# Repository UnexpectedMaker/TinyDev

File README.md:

# TinyDev
TinyDev Design Files

Inlcluded in this reposity:
- EagleCAD schematics and Board layout files (Eagle 9.1.1) 
- Exported Gerber files (Gerber 274X)

Enjoy!

# Back me on Patreon?
I love making and designing projects but sharing open source projects takes a lot of thought and time. I do it because I think it’s important to share knowledge and give back to the community like many have done before me.

If you find this project useful or want to see more open source projects like it, please consider backing me on Patreon to say thanks!

# Unexpected Maker
http://youtube.com/c/unexpectedmaker

http://twitter.com/unexpectedmaker

https://www.facebook.com/unexpectedmaker/

https://www.instagram.com/unexpectedmaker/

https://www.tindie.com/stores/seonr/

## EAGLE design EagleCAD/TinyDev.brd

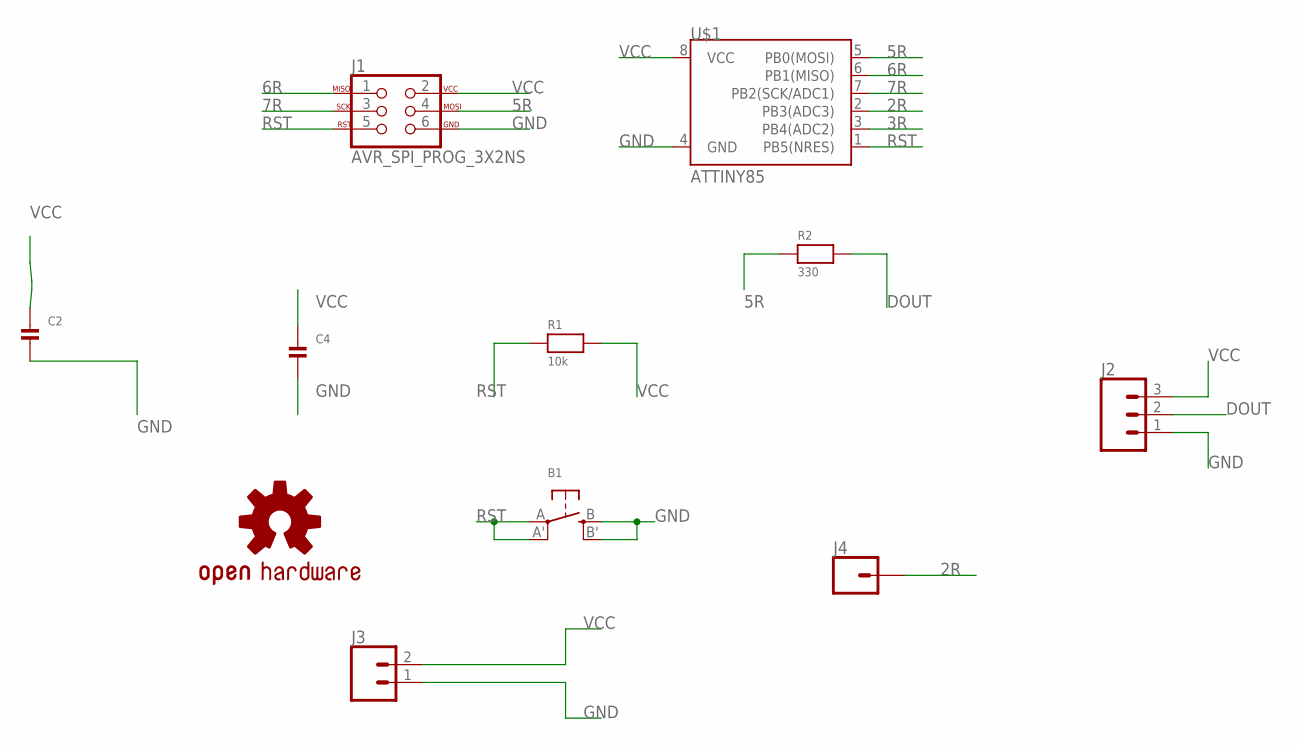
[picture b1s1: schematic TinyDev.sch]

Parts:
B1: SWITCH_TACT_SMT4.6X2.8; BTN_KMR2_4.6X2.8
C2, C4: CAP_CERAMIC_0805; _0805
J1: AVR_SPI_PROG_3X2NS; 2X3-NS
J2: CONN_031X03_NO_SILK; 1X03_NO_SILK
J3: CONN_021X02_NO_SILK; 1X02_NO_SILK
J4: CONN_01PTH_NO_SILK_KIT; 1X01NS_KIT
LOGO1: OSHW-LOGOS; OSHW-LOGO-S
R1: 10k; 0603-MINI
R2: 330; 0603-MINI
U$1: ATTINY85; SO08-EIAJ

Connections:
2R: J4.1, U$1.2 (PB3(ADC3))
3R: U$1.3 (PB4(ADC2))
5R: J1.4, R2.1, U$1.5 (PB0(MOSI))
6R: J1.1, U$1.6 (PB1(MISO))
7R: J1.3, U$1.7 (PB2(SCK/ADC1))
DOUT: J2.2, R2.2
GND: B1.B (S), B1.B' (S1), C2.2, C4.2, J1.6, J2.1, J3.1, U$1.4 (GND)
RST: B1.A, B1.A' (P1), J1.5, R1.1, U$1.1 (PB5(NRES))
VCC: C2.1, C4.1, J1.2, J2.3, J3.2, R1.2, U$1.8 (VCC)

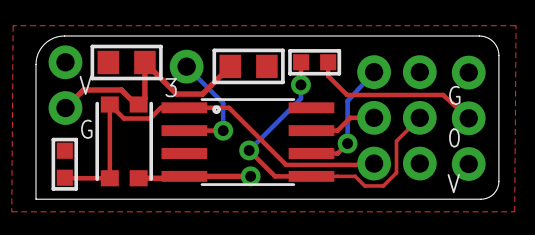
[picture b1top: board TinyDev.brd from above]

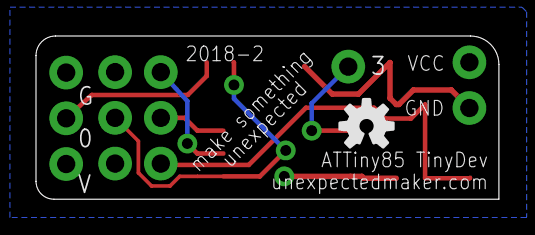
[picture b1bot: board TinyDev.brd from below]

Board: 2 copper layers, 25.7 x 9.1 mm, 11 parts (2 on the bottom side), 8 nets.

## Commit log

2018-07-25 Update README.md
    Added donate button
2018-07-25 Update README.md
    Updated donate text

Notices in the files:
parts and their libraries:
SparkFun: Licensing: CC v3.0 Share-Alike You are welcome to use this library for commercial purposes.
microbuilder: This work is placed in the public domain, and may be freely used for commercial and non-commercial work with the following conditions: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
